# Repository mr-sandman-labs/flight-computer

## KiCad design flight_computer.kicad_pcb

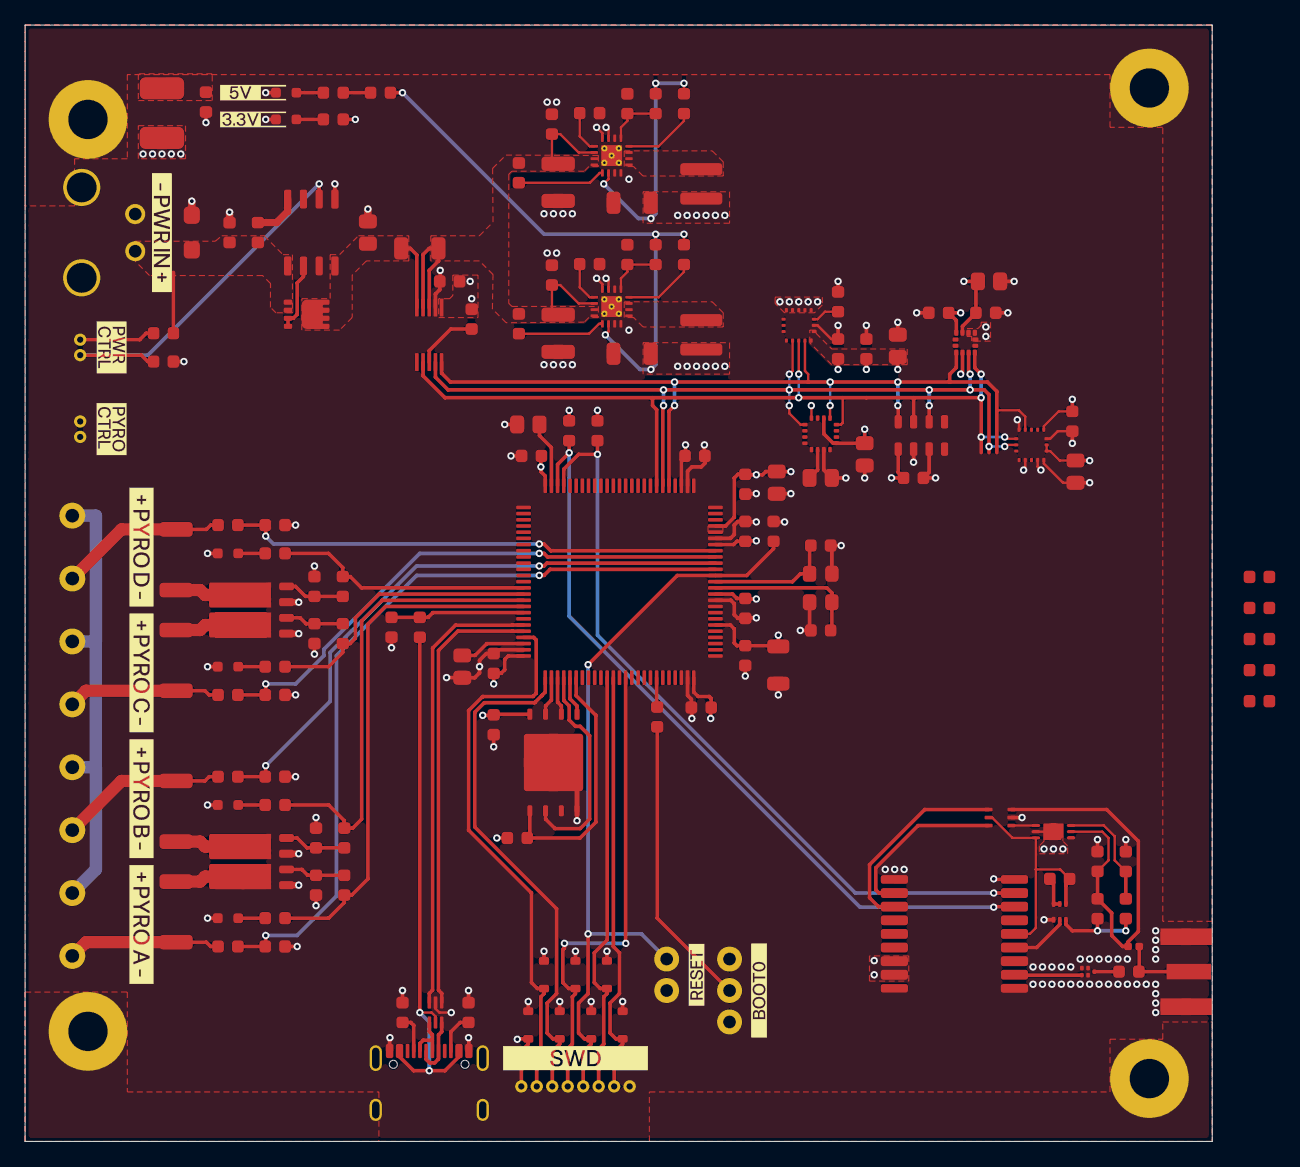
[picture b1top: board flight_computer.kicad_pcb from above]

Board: 4 copper layers, 95.9 x 90.2 mm, 166 parts (0 on the bottom side), 99 nets.

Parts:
C1, C4, C6, C8, C9, C10, C12, C13, C16, C17, C18, C21, C26, C29, C30, C34, C36, C39, C41, C43: 100nF; C_0603_Density_Nominal
C2, C3: 6pF; C_0603_Density_Nominal
C5, C7, C35: 2.2μF; C_0805_Density_Nominal
C11, C28, C42: 1μF; C_0805_Density_Nominal
C14, C15: 10μF; C_1210_Density_Nominal
C19, C20: 3.3nF; C_0603_Density_Nominal
C22: 4.7μF; C_1206_Density_Nominal
C23, C24: 22μF; C_1206_Density_Nominal
C25: 100nF; C_1812_Density_Nominal
C27, C31, C38: 10μF; C_0805_Density_Nominal
C32, C37: 10nF; C_0603_Density_Nominal
C33: 47pF; C_0603_Density_Nominal
C40: 0.47µF; C_0603_Density_Nominal
D1: SZSMF4L17CAT3G
D2, D3, D4, D5, D6, D7: Green; SML-D12P8WT86C
D8, D9, D10, D11, D12, D13, D14: SZESD7351HT1G
J1: 436500204
J2, J3: 0530480210
J4, J5, J6, J7: 398800302
J8: 0530480810
J9: USB4105-GF-A-120
J10: TSW-102-07-F-S
J11: TSW-103-07-F-S
J12: SMA-J-P-H-ST-EM1
L1, L2: 2.2μH; XGL4020-222MEC
L3: 27nH; L_0402_Density_Nominal
MH1, MH2, MH3, MH4: M3
Q4, Q5: IPG20N04S4L08ATMA1
Q6: SI1016CX-T1-GE3
Q7: DMT6007LFGQ-7
R1, R2, R5, R10, R12, R16, R22, R24, R28, R31, R33, R34, R54, R55, R56, R57, R58: 10kΩ; R_0603_Density_Nominal
R3, R13, R14, R51, R52: 100kΩ; R_0603_Density_Nominal
R4: 10mΩ; R_1206_Density_Nominal
R7, R8: 0Ω; R_0603_Density_Nominal
R9, R15, R23, R25, R26, R30: 1.8kΩ; R_0603_Density_Nominal
R11, R21, R27, R32: 47kΩ; R_0603_Density_Nominal
R17: 1.21MΩ; R_0603_Density_Nominal
R18, R20: 383kΩ; R_0603_Density_Nominal
R19: 2MΩ; R_0603_Density_Nominal
R29: 1MΩ; R_0603_Density_Nominal
R35, R36, R37, R38: 10Ω; R_2010_Density_Nominal
R39, R40, R41, R42, R43, R44, R45: 100Ω; R_0603_Density_Nominal
R46, R47: 5.1kΩ; R_0603_Density_Nominal
R48: 33kΩ; R_0603_Density_Nominal
R49: 82kΩ; R_0603_Density_Nominal
R50: 10Ω; R_0603_Density_Nominal
R53: 560Ω; R_0603_Density_Nominal
U1: STM32F405VGT7
U2: INA229AQDGSRQ1
U3, U4: TPS62130AQRGTRQ1
U5: S25FL256LAGNFM010
U6: USBLC6-2P6
U7: MMC5983MA
U8: AIS2IHTR
U9: MAX-M10S-00B
U10: LT6000IDCB#TRMPBF
U11: NC7WZ07P6X
U12: B39162B4300F210
U13: MS561101BA03-50
U14: IAM-20380HT
U15: H3LIS331DLTR
U16: LM74700QDRQ1
Y1: 25MHz; ECS-250-8-33Q-RES-TR
kibuzzard-6A2D8A19: G***; kibuzzard-6A2D8A19
kibuzzard-6A2D86D8: G***; kibuzzard-6A2D86D8
kibuzzard-6A2D86DB: G***; kibuzzard-6A2D86DB
kibuzzard-6A2D88AE: G***; kibuzzard-6A2D88AE
kibuzzard-6A2D88CA: G***; kibuzzard-6A2D88CA
kibuzzard-6A2D88D0: G***; kibuzzard-6A2D88D0
kibuzzard-6A2D88D5: G***; kibuzzard-6A2D88D5
kibuzzard-6A2D89E8: G***; kibuzzard-6A2D89E8
kibuzzard-6A2D888E: G***; kibuzzard-6A2D888E
kibuzzard-6A2D8804: G***; kibuzzard-6A2D8804
kibuzzard-6A2D8820: G***; kibuzzard-6A2D8820
kibuzzard-6A2DBB13: G***; kibuzzard-6A2DBB13

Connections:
+3.3V: C4.1, C6.1, C8.1, C9.1, C10.1, C11.1, C12.1, C13.1, C16.1, C21.1, C22.1, C23.1, C26.1, C28.1, C29.1, C30.1, C31.1, C34.1, C35.1, C36.1, C37.1, C38.1, C39.1, D14.1, J8.1, J11.1, L1.2, R5.1, R13.2, R17.1, R25.1, R26.1, R34.1, R43.1, R54.1, R55.1, R56.1, R57.1, R58.1, U1.6 (VBAT), U1.11 (VDD), U1.19 (VDD), U1.21 (VREF+), U1.22 (VDDA), U1.28 (VDD), U1.50 (VDD), U1.75 (VDD), U1.100 (VDD), U2.6 (VS), U3.14 (VOS), U5.8 (VCC), U7.2 (VDD), U7.13 (VDDIO), U8.9 (VDD), U8.10 (VDDIO), U9.7 (V_IO), U9.8 (VCC), U13.1 (VDD), U14.1 (VDDIO), U14.16 (VDD), U15.1 (VDDIO), U15.14 (VDD), U15.15 (Reserved)
+5V: C24.1, L2.2, R14.2, R19.1, R45.1, U4.14 (VOS)
/Microcontroller/BOOT0: R1.2, U1.94 (BOOT0)
/Microcontroller/CC1: J9.A5 (CC1), R47.1
/Microcontroller/CC2: J9.B5 (CC2), R46.1
/Microcontroller/RCC_OSC_IN: C2.1, U1.12 (PH0), Y1.1
/Microcontroller/RCC_OSC_OUT: C3.1, U1.13 (PH1), Y1.3
/Microcontroller/USB_CONN_D+: J9.A7 (DN1), J9.B7 (DN2), U6.4 (I/O2)
/Microcontroller/USB_CONN_D-: J9.A6 (DP1), J9.B6 (DP2), U6.6 (I/O1)
/Microcontroller/V_CAP1: C7.1, U1.49 (VCAP_1)
/Microcontroller/V_CAP2: C5.1, U1.73 (VCAP_2)
/Power/+3.3V_EN: R7.2, U3.13 (EN)
/Power/+3.3V_FB: R17.2, R18.1, U3.5 (FB)
/Power/+3.3V_PG: R13.1, U3.4 (PG)
/Power/+3.3V_SS/TR: C19.1, U3.9 (SS/TR)
/Power/+3.3V_SW: L1.1, U3.1 (SW), U3.2 (SW), U3.3 (SW)
/Power/+5V_EN: R8.2, U4.13 (EN)
/Power/+5V_FB: R19.2, R20.1, U4.5 (FB)
/Power/+5V_PG: R14.1, U4.4 (PG)
/Power/+5V_SS/TR: C20.1, U4.9 (SS/TR)
/Power/+5V_SW: L2.1, U4.1 (SW), U4.2 (SW), U4.3 (SW)
/Power/VCAP: C43.2, U16.4 (VCAP)
/Power/VIN_PROT: C42.1, Q7.D, R4.1, U2.10 (IN+), U16.8 (CATHODE)
/Power/VSENSE: C14.1, C15.1, C17.1, C18.1, J3.1, R4.2, R7.1, R8.1, U2.8 (VBUS), U2.9 (IN-), U3.10 (AVIN), U3.11 (PVIN), U3.12 (PVIN), U4.10 (AVIN), U4.11 (PVIN), U4.12 (PVIN)
/RF/ANT_DETECT: U9.2 (ANT_DETECT), U11.6 (Y1)
/RF/ANT_SHORT: U9.3 (ANT_SHORT), U11.4 (Y2)
/RF/LNA_EN: Q6.2 (G), U9.13 (LNA_EN)
/RF/RF_IN: U9.11 (RF_IN), U12.4 (Output)
/Sensors/GYRO_REGOUT: C40.1, U14.14 (REGOUT)
/Sensors/MAG_CAP: C27.1, U7.10 (CAP)
CHASSIS: C25.2, J1.MP, J9.SH, MH1.1 (MH_1), MH2.1 (MH_1), MH3.1 (MH_1), MH4.1 (MH_1), R29.2
FIRE_A: R9.1, R39.1, U1.67 (PA8)
FIRE_B: R15.1, R40.1, U1.66 (PC9)
FIRE_C: R23.1, R41.1, U1.65 (PC8)
FIRE_D: R30.1, R42.1, U1.64 (PC7)
GND: C1.2, C2.2, C3.2, C4.2, C5.2, C6.2, C7.2, C8.2, C9.2, C10.2, C11.2, C12.2, C13.2, C14.2, C15.2, C16.2, C17.2, C18.2, C19.2, C20.2, C21.2, C22.2, C23.2, C24.2, C25.1, C26.2, C27.2, C28.2, C29.2, C30.2, C31.2, C32.2, C34.2, C35.2, C36.2, C37.2, C38.2, C39.2, C40.2, C41.2, C42.2, D1.2, D2.1, D3.1, D4.1, D5.1, D6.1, D7.1, D8.2, D9.2, D10.2, D11.2, D12.2, D13.2, D14.2, J1.2, J8.8, J9.A1 (GND), J9.A12 (GND), J9.B1 (GND), J9.B12 (GND), J10.2, J11.3, J12.2, Q4.1 (S), Q4.3 (S), Q5.1 (S), Q5.3 (S), Q6.1 (S), R3.2, R10.2, R12.2, R16.2, R18.2, R20.2, R22.2, R24.2, R28.2, R29.1, R31.2, R33.2, R46.2, R47.2, R49.2, R52.2, U1.10 (VSS), U1.20 (VSSA), U1.27 (VSS), U1.74 (VSS), U1.99 (VSS), U2.7 (GND), U3.6 (AGND), U3.7 (FSW), U3.8 (DEF), U3.15 (PGND), U3.16 (PGND), U3.17 (EP), U4.6 (AGND), U4.7 (FSW), U4.8 (DEF), U4.15 (PGND), U4.16 (PGND), U4.17 (EP), U5.4 (VSS), U5.9 (EP), U6.2 (GND), U7.11 (GND), U8.6 (GND), U8.7 (RES), U8.8 (GND), U9.1 (GND), U9.10 (GND), U9.12 (GND), U10.5 (V-), U10.7 (EP), U11.2 (GND), U12.2 (GND), U12.3 (GND), U12.5 (GND), U13.2 (PS), U13.3 (GND), U14.9 (RESV), U14.10 (RESV), U14.11 (RESV), U14.12 (RESV), U14.13 (GND), U14.15 (RESV), U15.5 (GND), U15.10 (Reserved), U15.12 (GND), U15.13 (GND), U15.16 (GND), U16.1 (GND), Y1.2 (GND), Y1.4 (GND)
I2C2.SCL: R25.2, U1.47 (PB10), U9.17 (SCL)
I2C2.SDA: R26.2, U1.48 (PB11), U9.16 (SDA)
MEM_RESET: U1.77 (PA15), U5.7 (IO3)
unnamed: C33.2, J12.1, L3.1
unnamed: D2.2, R39.2
unnamed: D3.2, R40.2
unnamed: D4.2, R41.2
unnamed: D5.2, R42.2
unnamed: D6.2, R43.2
unnamed: D7.2, R44.2
unnamed: J2.1, R2.2
unnamed: J3.2, J4.1, J5.1, J6.1, J7.1
unnamed: J4.2, R11.1, R35.1
unnamed: J5.2, R21.1, R36.1
unnamed: J6.2, R27.1, R37.1
unnamed: J7.2, R32.1, R38.1
unnamed: J11.2, R1.1
unnamed: Q4.7 (D), Q4.8 (D), R35.2
unnamed: Q4.2 (G), R9.2, R10.1
unnamed: Q4.5 (D), Q4.6 (D), R36.2
unnamed: Q4.4 (G), R15.2, R16.1
unnamed: Q5.7 (D), Q5.8 (D), R37.2
unnamed: Q5.2 (G), R23.2, R24.1
unnamed: Q5.5 (D), Q5.6 (D), R38.2
unnamed: Q5.4 (G), R30.2, R31.1
unnamed: Q6.5 (G), Q6.6 (D), R51.1
unnamed: Q6.3 (D), R50.2, R53.1
unnamed: R44.1, R45.2
unnamed: R48.2, R49.1, U1.68 (PA9)
unnamed: R52.1, R53.2, U10.3 (IN+)
unnamed: C32.1, L3.2, R50.1, U10.2 (IN-), U11.3 (A2)
unnamed: U10.4 (OUT), U11.1 (A1)
unnamed: C33.1, U12.1 (Input)
unnamed: J2.2, R3.1, U16.2 (EN)
unnamed: Q7.G, U16.6 (GATE)
POW_MON_INT: R5.2, U2.3 (ALERT)
SENSE_A: R11.2, R12.1, U1.15 (PC0)
SENSE_B: R21.2, R22.1, U1.16 (PC1)
SENSE_C: R27.2, R28.1, U1.17 (PC2)
SENSE_D: R32.2, R33.1, U1.18 (PC3)
SPI1.MISO: U1.31 (PA6), U2.4 (MISO), U7.5 (SPI_SDO), U8.3 (SDO), U13.6 (SDO), U14.4 (SDO), U15.7 (SDO)
SPI1.MOSI: U1.32 (PA7), U2.2 (MOSI), U7.16 (SPI_SDI), U8.4 (SDI), U13.7 (SDI), U14.3 (SDI), U15.6 (SDI)
SPI1.SCLK: U1.30 (PA5), U2.5 (SCLK), U7.1 (SPI_SCK), U8.1 (SPC), U13.8 (SCLK), U14.2 (SPC), U15.4 (SPC)
SPI3.MISO: U1.79 (PC11), U5.2 (SO)
SPI3.MOSI: U1.80 (PC12), U5.5 (SI)
SPI3.SCLK: U1.78 (PC10), U5.6 (SCK)
SWD.NRST: C1.1, D10.1, J8.5, J10.1, U1.14 (NRST)
SWD.SWCLK: D12.1, J8.3, U1.76 (PA14)
SWD.SWDIO: D13.1, J8.2, U1.72 (PA13)
SWD.SWO: D11.1, J8.4, U1.89 (PB3)
USART2.RX: D8.1, J8.7, U1.87 (PD6)
USART2.TX: D9.1, J8.6, U1.86 (PD5)
USB.D+: U1.71 (PA12), U6.1 (I/O1)
USB.D-: U1.70 (PA11), U6.3 (I/O2)
VCC RF: Q6.4 (S), R51.2, U9.14 (VCC_RF), U10.6 (V+), U11.5 (VCC)
VIN: C41.1, C43.1, D1.1, J1.1, Q7.S, R2.1, U16.5 (ANODE)
VUSB: J9.A4 (VBUS), J9.A9 (VBUS), J9.B4 (VBUS), J9.B9 (VBUS), R48.1, U6.5 (VBUS)
~BAR_CS: R54.2, U13.4 (CSB), U13.5 (CSB)
~GYRO_CS: R56.2, U14.5 (CS)
~MAG_CS: R55.2, U7.4 (~SPI_CS)
~MEM_CS: R34.2, U1.81 (PD0), U5.1 (CS)
~PREC_ACCEL_CS: R57.2, U8.2 (CS)
~SHOCK_ACCEL_CS: R58.2, U15.8 (CS)

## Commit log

2026-06-13 Remove useless folders
2026-06-13 Update images workflow to use generic name
2026-06-13 Update releaser
2026-06-13 Update board images
2026-06-13 Update to power section
2026-06-13 Update workflows
2026-06-13 Update board images [88bcb92]
2026-06-13 Update workflows and rename them
2026-06-13 Move component to test workflows
2026-06-13 Update board images [8ed35ce]
2026-06-13 Add README
2026-06-13 Update board images [75ed3b0]
2026-06-14 Add initial layout for the GNSS receiver
2026-06-14 Update board images [02bf611]
2026-06-14 Improve board grounding for RF
2026-06-14 Update board images [301fe3e]
2026-06-14 Fix copper pour rule inconsistencies
2026-06-14 Update board images [851bdfc]
2026-06-14 - On push in main create a new set of documents - On release fix images - Update README to use correct images
2026-06-14 Fix typo
2026-06-14 Update board images [dbde93b]
2026-06-15 Major fix: move from a flat to a hierarchical architecture for schematic.
2026-06-15 Remove images
2026-06-15 Update board images [f69413a]
2026-06-15 Fix README
2026-06-15 Update workflows to use wLight for schematic export
2026-06-15 Update board images [9bae6d3]
2026-06-15 Fix theme name
2026-06-15 Update board images [fabf8d3]
2026-06-15 Change theme to black & white
2026-06-15 Update board images [a5016d6]
2026-06-15 Added measurements to PCB view
2026-06-15 Update board images [e3fdb58]
2026-06-16 Improve PCB measurements
2026-06-16 Update dependencies to fix AT-SPI error, embed fonts in project
2026-06-16 Update board images [a53ee89]
2026-06-21 Moved GNSS to bottom right of the board, added sensor ro SPI bus, improved chassis ring to cover more parts of the board
2026-06-21 Fix workflow name
2026-06-21 Update board images [803d3a7]
2026-06-21 Added M3 mounting holes to schematic, replaced them in PCB layout so they appear in the output documents
2026-06-21 Update board images [ad04d1f]
2026-06-22 Change mounting hole connection type to solid
2026-06-22 Place pullup resistors for SPI bus
2026-06-22 Update board images [289f2f0]

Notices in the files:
parts and their libraries:
LICENSE: CERN-OHL-S
